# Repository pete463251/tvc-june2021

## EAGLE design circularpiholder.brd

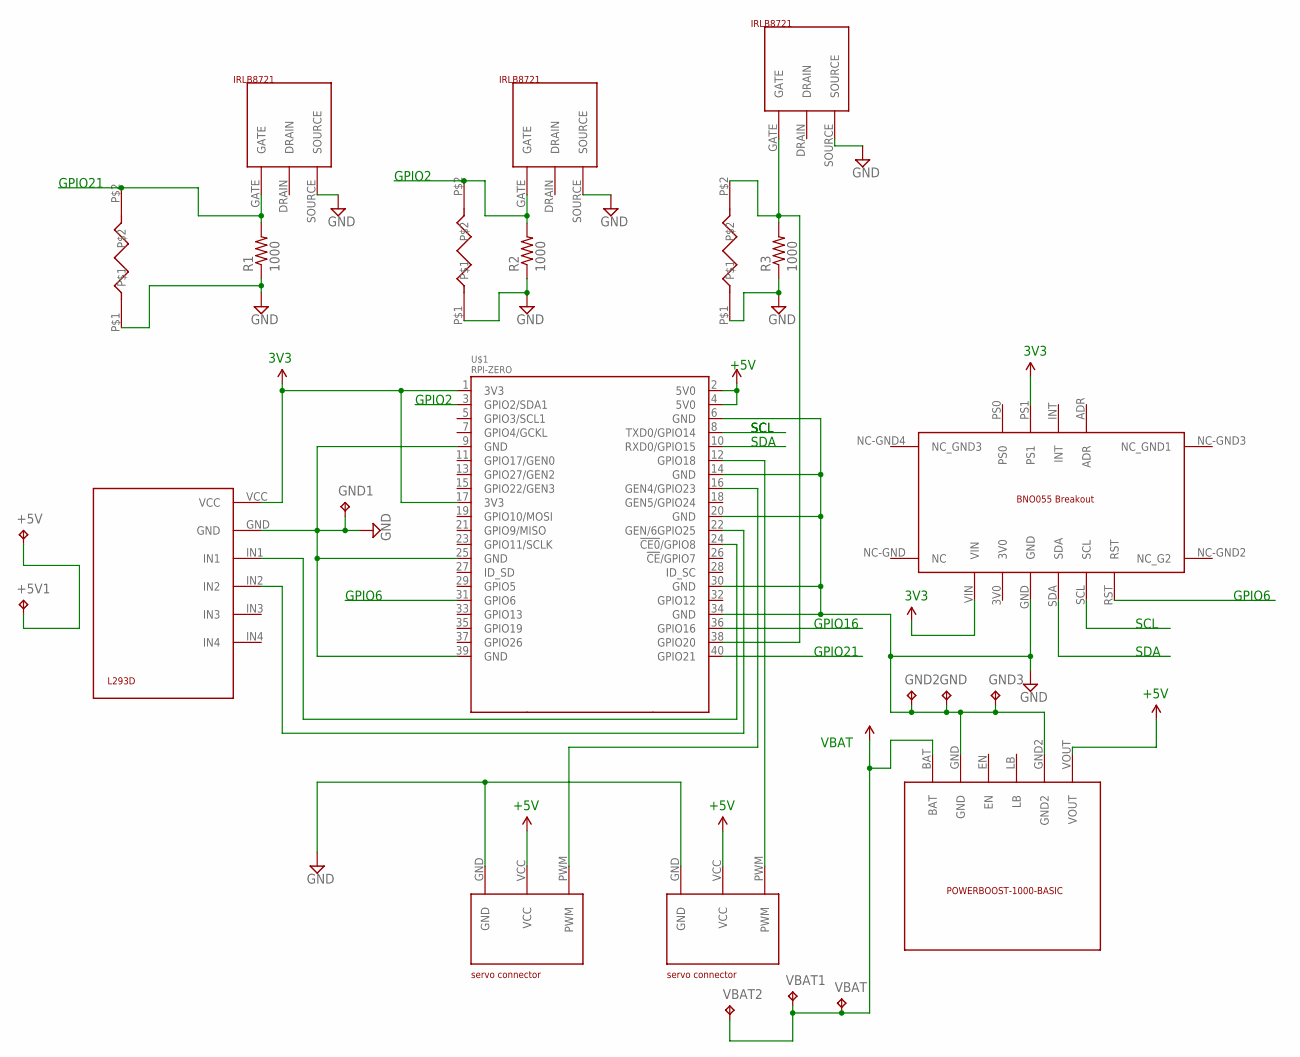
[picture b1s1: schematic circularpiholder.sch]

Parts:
+5V, +5V1: TPTP20SQ; TP20SQ
GND, GND1, GND2, GND3: TPTP20SQ; TP20SQ
R1, R2, R3: 1000; 0603-RES
U$1: RPI-ZERO; RASPBERRYPI_BASTELSTUBE_V13_RASPI_BOARD_B+_FULL
U$2: BNO055-BREAKOUT; BNO055BREAKOUT
U$3: POWERBOOST1000-BASIC
U$4, U$5, U$6: MOSFET-IRLB872; MOSFET-IRLB8721
U$7: L293D-DUALMOTORCONTROL
U$8, U$9: SERVO-3PIN-CONN
U$10, U$11, U$12: SURFACEMNT-RESSURFACEMNT; SURFACEMNT-RES
VBAT, VBAT1, VBAT2: TPTP20SQ; TP20SQ

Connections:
3V3: U$1.1 (3V3), U$1.17 (3V3), U$2.PS1, U$2.VIN, U$7.VCC
+5V: +5V.TP, +5V1.TP, U$1.2 (5V0), U$1.4 (5V0), U$3.VOUT, U$8.VCC, U$9.VCC
GPIO2: R2.2, U$1.3 (GPIO2/SDA1), U$5.GATE, U$11.P$2
GPIO6: U$1.31 (GPIO6), U$2.RST
GPIO16: U$1.36 (GPIO16)
GPIO21: R1.2, U$1.40 (GPIO21), U$6.GATE, U$10.P$2
GROUND: GND.TP, GND1.TP, GND2.TP, GND3.TP, R1.1, R2.1, R3.1, U$1.6 (GND), U$1.9 (GND), U$1.14 (GND), U$1.20 (GND), U$1.25 (GND), U$1.30 (GND), U$1.34 (GND), U$1.39 (GND), U$2.GND, U$3.GND, U$3.GND2, U$4.SOURCE, U$5.SOURCE, U$6.SOURCE, U$7.GND, U$8.GND, U$9.GND, U$10.P$1, U$11.P$1, U$12.P$1
unnamed: R3.2, U$1.38 (GPIO20), U$4.GATE, U$12.P$2
unnamed: U$1.12 (GPIO18), U$9.PWM
unnamed: U$1.16 (GEN4/GPIO23), U$8.PWM
unnamed: U$1.24 (!CE0!/GPIO8), U$7.IN1
unnamed: U$1.22 (GEN/6GPIO25), U$7.IN2
SCL: U$1.8 (TXD0/GPIO14), U$2.SCL
SDA: U$1.10 (RXD0/GPIO15), U$2.SDA
VBAT: U$3.BAT, VBAT.TP, VBAT1.TP, VBAT2.TP

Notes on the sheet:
+5V
VBAT
3V3
GPIO6
SCL
SDA
GPIO16
GPIO2
GPIO21

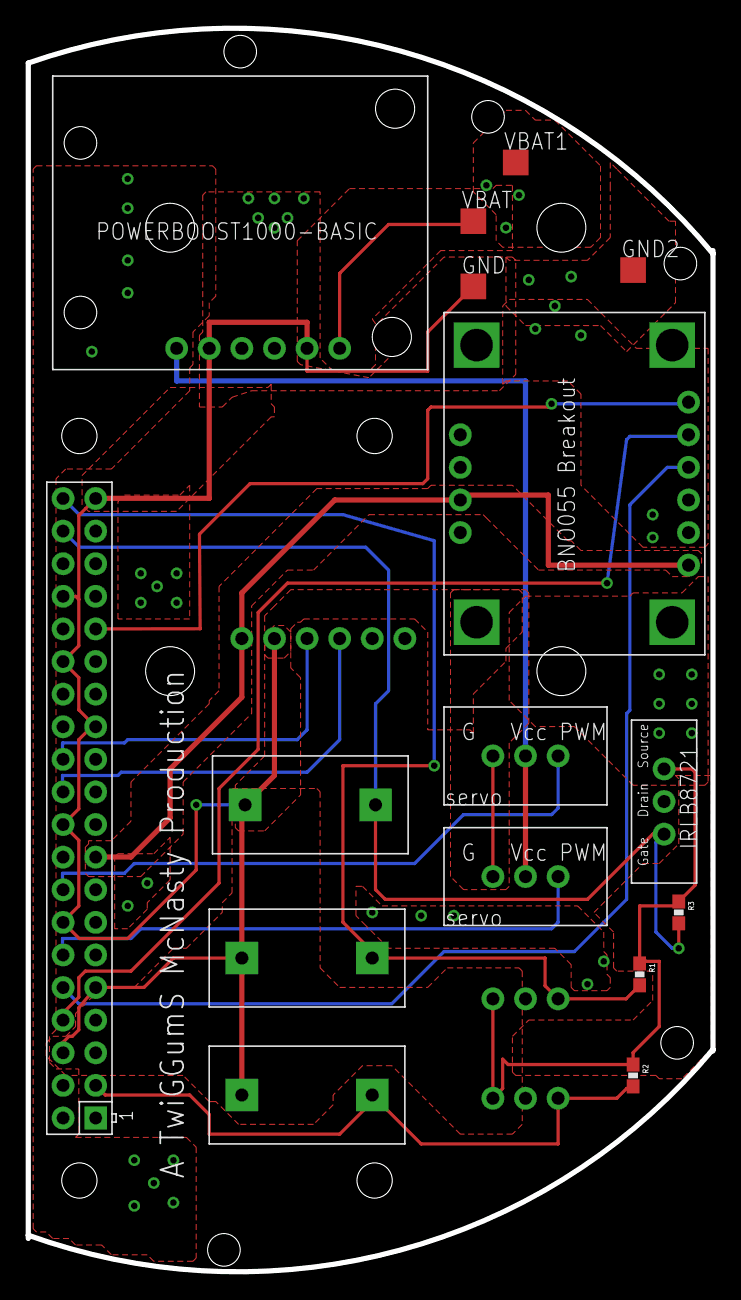
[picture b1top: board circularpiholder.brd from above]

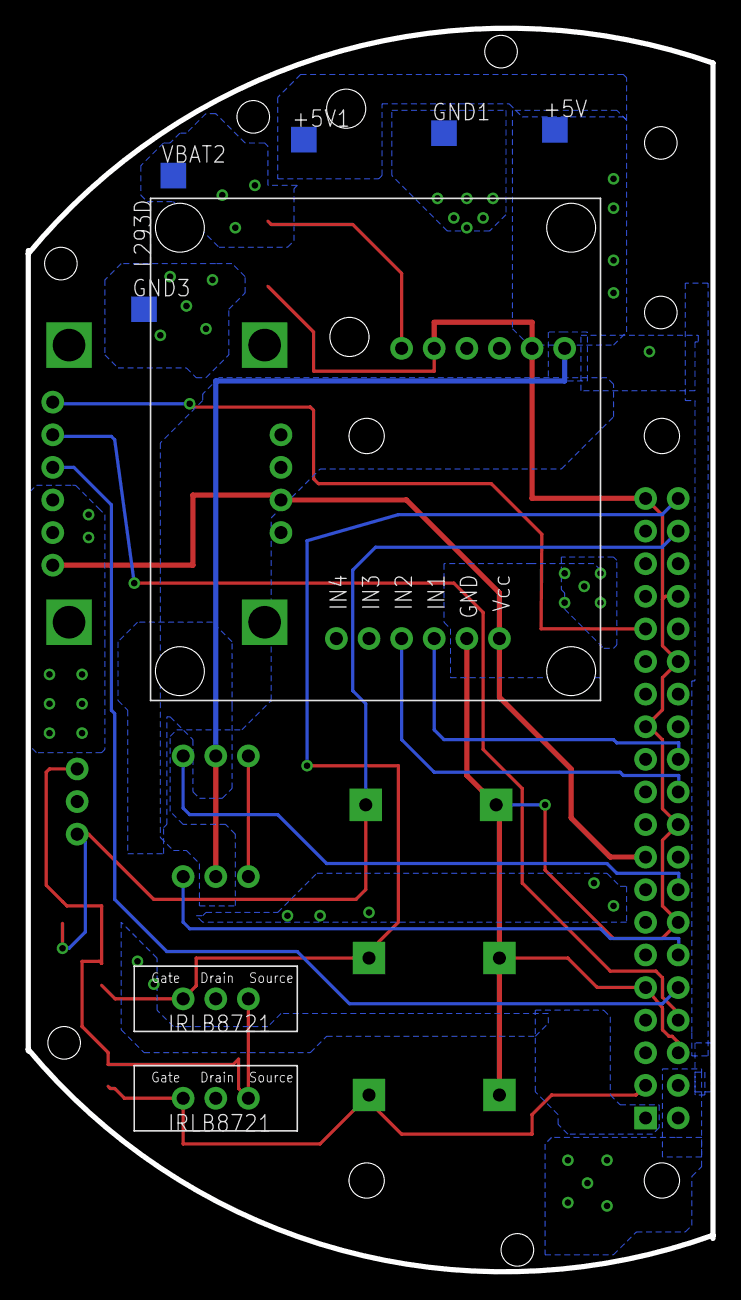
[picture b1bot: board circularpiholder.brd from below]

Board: 2 copper layers, 53.3 x 96.9 mm, 24 parts (8 on the bottom side), 14 nets.

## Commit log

2021-06-22 Add files via upload
    launchH13.py and launchF10.py are the code that runs on the raspberry pi
    .brd and .sch are eagle files
    IMU-flight6.txt and -7.txt are the raw data saved during the flight
    plotIMUdata***** is used to plot outptuts
    schematic-drawing.png is hand drawn schematic

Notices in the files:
parts and their libraries:
SparkFun-Passives: Licensing: Creative Commons ShareAlike 4.0 International - https://creativecommons.org/licenses/by-sa/4.0
